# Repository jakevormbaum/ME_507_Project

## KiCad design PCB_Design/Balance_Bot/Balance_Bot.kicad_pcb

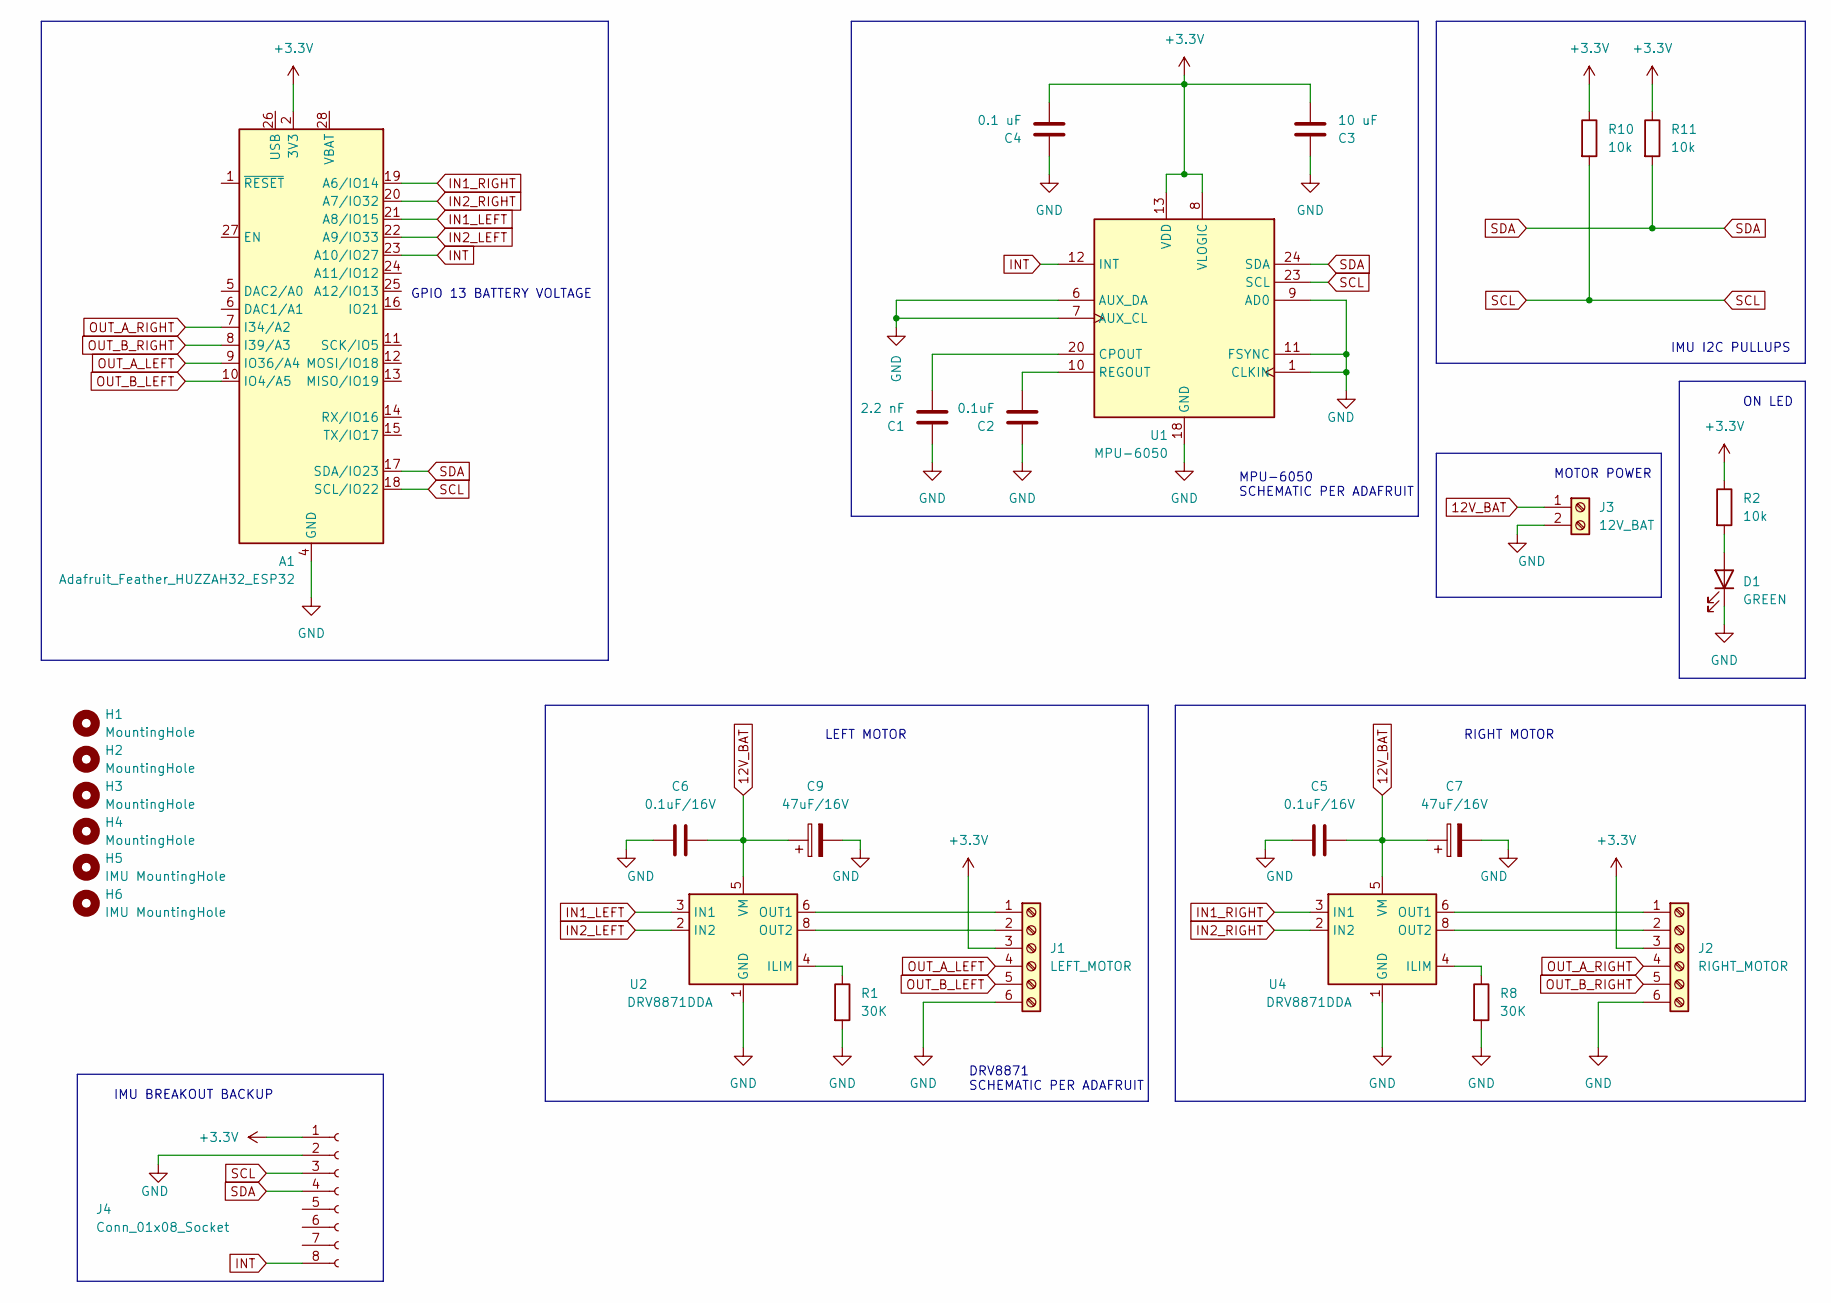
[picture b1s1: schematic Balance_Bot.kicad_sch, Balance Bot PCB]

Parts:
A1: Adafruit_Feather_HUZZAH32_ESP32; Adafruit_Feather
C1: 2.2 nF; C_0805_2012Metric
C2: 0.1uF; C_0805_2012Metric
C3: 10 uF; C_0805_2012Metric
C4: 0.1 uF; C_0805_2012Metric
C5, C6: 0.1uF/16V; C_0805_2012Metric
C7, C9: 47uF/16V; CP_Radial_D6.3mm_P2.50mm
D1: GREEN; LED_0805_2012Metric
H1, H2, H3, H4: MountingHole; MountingHole_3.2mm_M3
H5, H6: IMU MountingHole; MountingHole_3.2mm_M3
J1: LEFT_MOTOR; TerminalBlock_Phoenix_MPT-0,5-6-2.54_1x06_P2.54mm_Horizontal
J2: RIGHT_MOTOR; TerminalBlock_Phoenix_MPT-0,5-6-2.54_1x06_P2.54mm_Horizontal
J3: 12V_BAT; TerminalBlock_Phoenix_MPT-0,5-2-2.54_1x02_P2.54mm_Horizontal
J4: Conn_01x08_Socket; PinSocket_1x08_P2.54mm_Vertical
R1, R8: 30K; R_0805_2012Metric
R2, R10, R11: 10k; R_0805_2012Metric
U1: MPU-6050; InvenSense_QFN-24_4x4mm_P0.5mm
U2, U4: DRV8871DDA; Texas_HTSOP-8-1EP_3.9x4.9mm_P1.27mm_EP2.95x4.9mm_Mask2.4x3.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

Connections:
12V_BAT: C5.1, C6.1, C7.1, C9.1, J3.1, U2.5 (VM), U4.5 (VM)
+3.3V: A1.2 (3V3), C3.1, C4.1, J1.3, J2.3, J4.1, R2.1, R10.1, R11.1, U1.8 (VLOGIC), U1.13 (VDD)
GND: A1.4 (GND), C1.1, C2.1, C3.2, C4.2, C5.2, C6.2, C7.2, C9.2, D1.1 (K), J1.6, J2.6, J3.2, J4.2, R1.2, R8.2, U1.1 (CLKIN), U1.6 (AUX_DA), U1.7 (AUX_CL), U1.9 (AD0), U1.11 (FSYNC), U1.18 (GND), U2.1 (GND), U2.7 (GND), U2.9 (GND), U4.1 (GND), U4.7 (GND), U4.9 (GND)
IN1_LEFT: A1.21 (A8/IO15), U2.3 (IN1)
IN1_RIGHT: A1.19 (A6/IO14), U4.3 (IN1)
IN2_LEFT: A1.22 (A9/IO33), U2.2 (IN2)
IN2_RIGHT: A1.20 (A7/IO32), U4.2 (IN2)
INT: A1.23 (A10/IO27), J4.8, U1.12 (INT)
unnamed: D1.2 (A), R2.2
unnamed: J1.1, U2.6 (OUT1)
unnamed: J1.2, U2.8 (OUT2)
unnamed: J2.1, U4.6 (OUT1)
unnamed: J2.2, U4.8 (OUT2)
unnamed: C1.2, U1.20 (CPOUT)
unnamed: C2.2, U1.10 (REGOUT)
unnamed: R1.1, U2.4 (ILIM)
unnamed: R8.1, U4.4 (ILIM)
OUT_A_LEFT: A1.9 (IO36/A4), J1.4
OUT_A_RIGHT: A1.7 (I34/A2), J2.4
OUT_B_LEFT: A1.10 (IO4/A5), J1.5
OUT_B_RIGHT: A1.8 (I39/A3), J2.5
SCL: A1.18 (SCL/IO22), J4.3, R10.2, U1.23 (SCL)
SDA: A1.17 (SDA/IO23), J4.4, R11.2, U1.24 (SDA)

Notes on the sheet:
ON LED
GPIO 13 BATTERY VOLTAGE
IMU BREAKOUT BACKUP
RIGHT MOTOR
IMU I2C PULLUPS
MPU-6050 SCHEMATIC PER ADAFRUIT
MOTOR POWER
DRV8871 SCHEMATIC PER ADAFRUIT
LEFT MOTOR

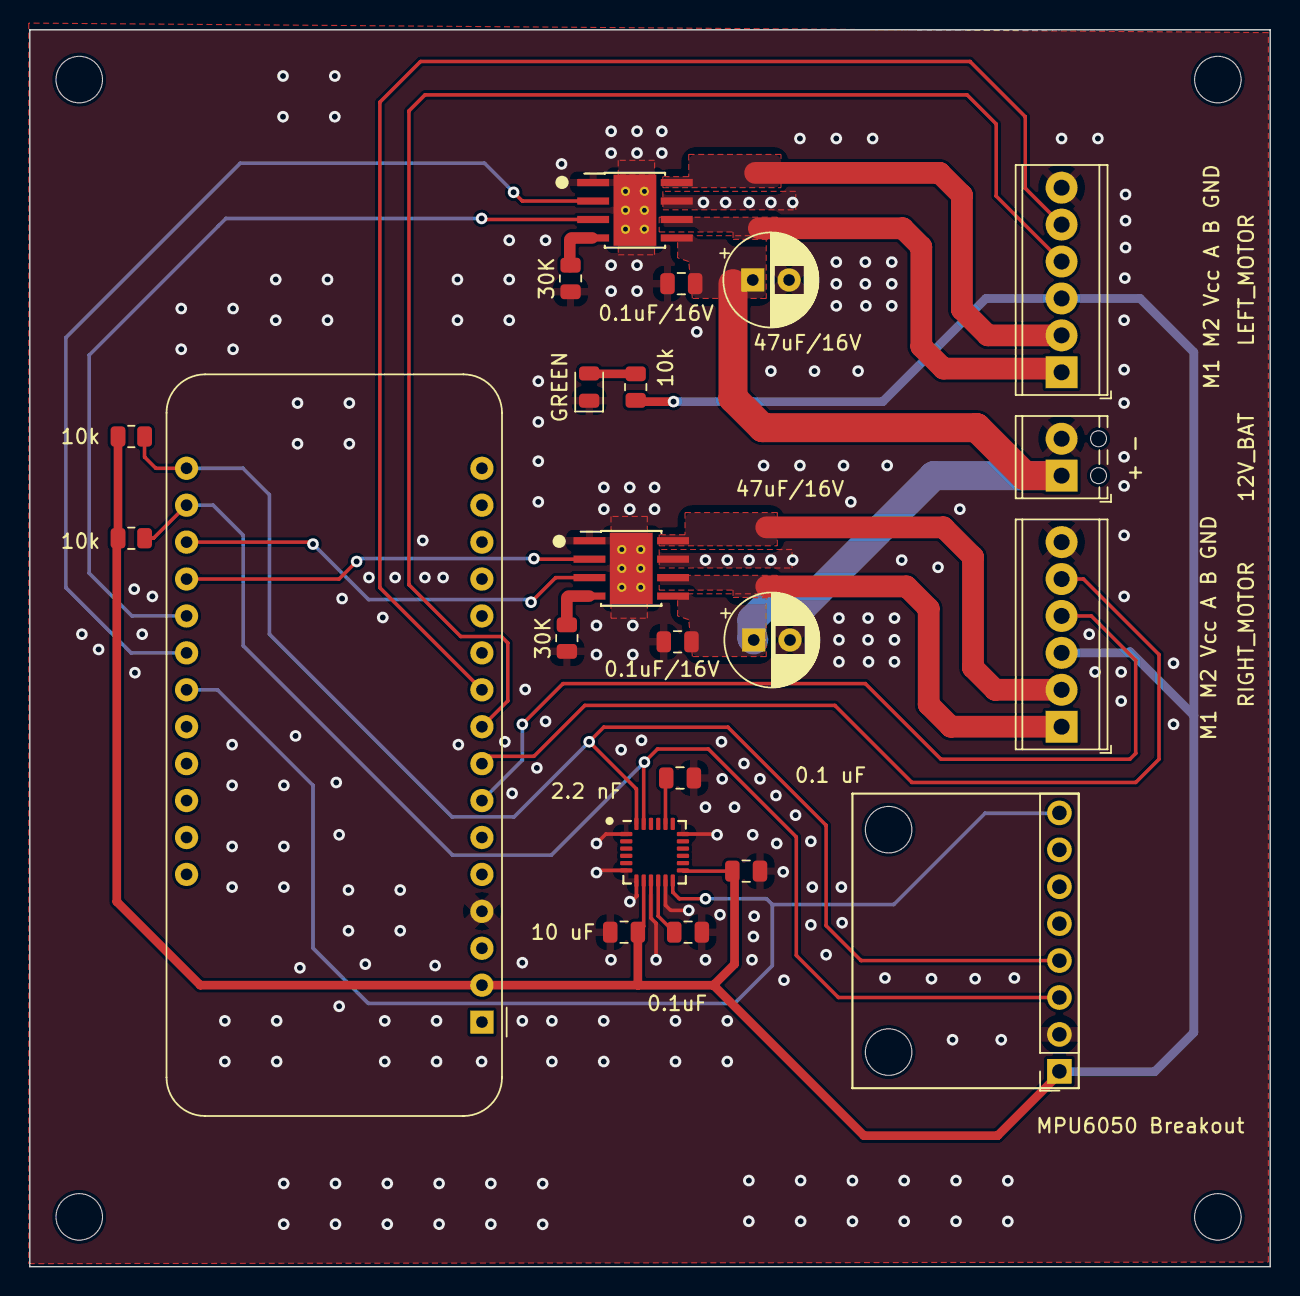
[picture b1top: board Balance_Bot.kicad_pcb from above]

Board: 2 copper layers, 85.3 x 85.1 mm, 28 parts (0 on the bottom side), 23 nets.

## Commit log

2023-10-19 Code and simulation
2023-10-26 KiCad
2023-10-26 Code and KiCad
2023-10-27 File org
2023-10-29 Pinout photos
2023-10-29 board design
2023-10-29 board stuff
2023-10-29 boards
2023-10-29 board
2023-11-08 PCB update
    Thickened some power traces to 24mil
    Added white dot next to GND pins on motor drivers to tell us orientation
    Added square showing MPU breakout orientation
2023-11-09 final
2023-11-16 final board
2023-11-29 code
2023-12-01 code and cad
2023-12-08 Website
    Program that creates a website for the ESP32 that displays angles from the IMU
2023-12-12 Doxygen Style Comments
    Filled out files with doxygen comments
2023-12-13 References to external libraries used doxygen style
    Updates top doxygen comment to reference the libraries used externally
2023-12-13 Ran doxygen for balance bot
    generated doxygen documentation
2023-12-13 Doxygen for ESP32 Web Server Program
    doxy generated documentation for esp32 web server program, kept it separate from main bot program
2023-12-13 Simulation scratch
